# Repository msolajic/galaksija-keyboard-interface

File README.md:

# galaksija-keyboard-interface
Keyboard interface for Galaksija computer using Arduino Nano and MT8816 crosspoint switch

I will upload the code later, it is based on https://github.com/Hartland/C64-Keyboard

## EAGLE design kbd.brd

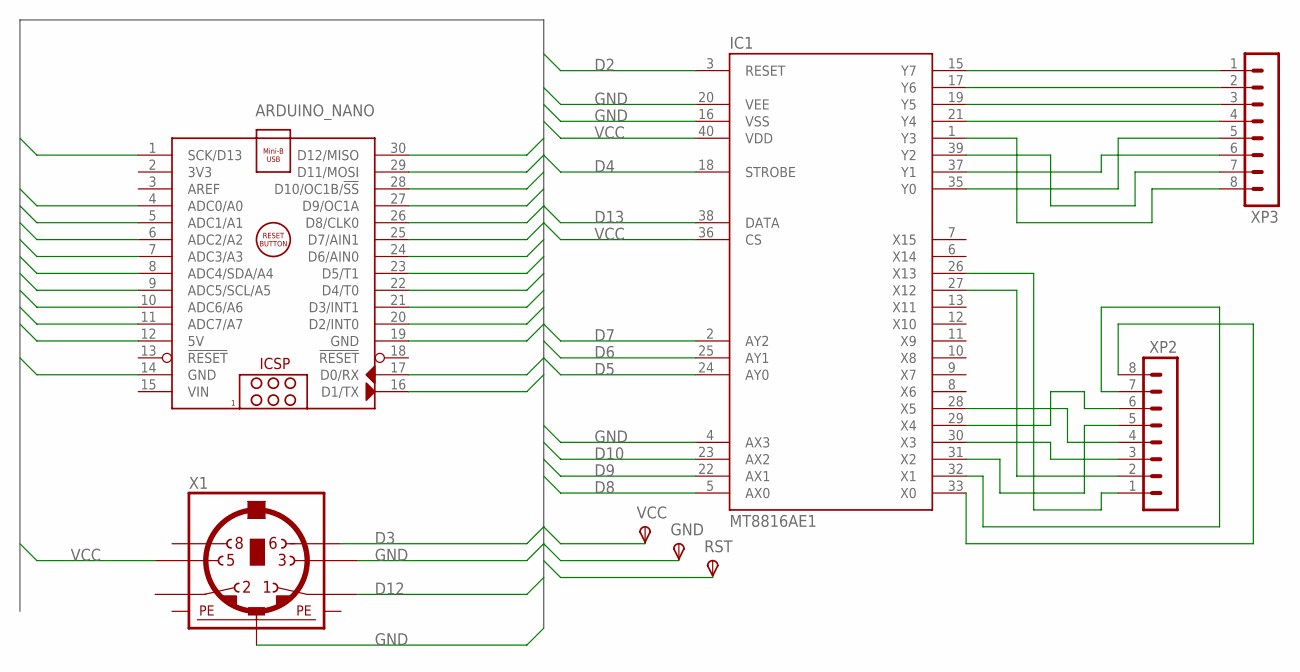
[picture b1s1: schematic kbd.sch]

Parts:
ARDUINO_NANO: ARDUINO_NANO
GND: TPSPAD1-13; P1-13
IC1: MT8816AE1; DIL40
RST: TPSPAD1-13; P1-13
VCC: TPSPAD1-13; P1-13
X1: MINI_DIN_6; M_DIN6
XP2, XP3: MA08-1

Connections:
A0: ARDUINO_NANO.4 (ADC0/A0), RST.TP
A1: ARDUINO_NANO.5 (ADC1/A1)
A2: ARDUINO_NANO.6 (ADC2/A2)
A3: ARDUINO_NANO.7 (ADC3/A3)
A4: ARDUINO_NANO.8 (ADC4/SDA/A4)
A5: ARDUINO_NANO.9 (ADC5/SCL/A5)
A6: ARDUINO_NANO.10 (ADC6/A6)
A7: ARDUINO_NANO.11 (ADC7/A7)
D0: ARDUINO_NANO.17 (D0/RX)
D1: ARDUINO_NANO.16 (D1/TX)
D2: ARDUINO_NANO.20 (D2/INT0), IC1.3 (RESET)
D3: ARDUINO_NANO.21 (D3/INT1), X1.6
D4: ARDUINO_NANO.22 (D4/T0), IC1.18 (STROBE)
D5: ARDUINO_NANO.23 (D5/T1), IC1.24 (AY0)
D6: ARDUINO_NANO.24 (D6/AIN0), IC1.25 (AY1)
D7: ARDUINO_NANO.25 (D7/AIN1), IC1.2 (AY2)
D8: ARDUINO_NANO.26 (D8/CLK0), IC1.5 (AX0)
D9: ARDUINO_NANO.27 (D9/OC1A), IC1.22 (AX1)
D10: ARDUINO_NANO.28 (D10/OC1B/!SS), IC1.23 (AX2)
D11: ARDUINO_NANO.29 (D11/MOSI)
D12: ARDUINO_NANO.30 (D12/MISO), X1.1
D13: ARDUINO_NANO.1 (SCK/D13), IC1.38 (DATA)
GND: ARDUINO_NANO.14 (GND), ARDUINO_NANO.19 (GND), GND.TP, IC1.4 (AX3), IC1.16 (VSS), IC1.20 (VEE), X1.3, X1.SH2 (PE2)
unnamed: IC1.15 (Y7), XP3.1
unnamed: IC1.17 (Y6), XP3.2
unnamed: IC1.19 (Y5), XP3.3
unnamed: IC1.21 (Y4), XP3.4
unnamed: IC1.35 (Y0), XP3.5
unnamed: IC1.37 (Y1), XP3.6
unnamed: IC1.39 (Y2), XP3.7
unnamed: IC1.1 (Y3), XP3.8
unnamed: IC1.27 (X12), XP2.2
unnamed: IC1.30 (X3), XP2.3
unnamed: IC1.28 (X5), XP2.4
unnamed: IC1.31 (X2), XP2.5
unnamed: IC1.29 (X4), XP2.6
unnamed: IC1.32 (X1), XP2.7
unnamed: IC1.33 (X0), XP2.8
unnamed: IC1.26 (X13), XP2.1
PE1: X1.SH1 (PE1)
PE3: X1.SH3 (PE3)
VCC: ARDUINO_NANO.12 (5V), IC1.36 (CS), IC1.40 (VDD), VCC.TP, X1.5
VIN: ARDUINO_NANO.15 (VIN)

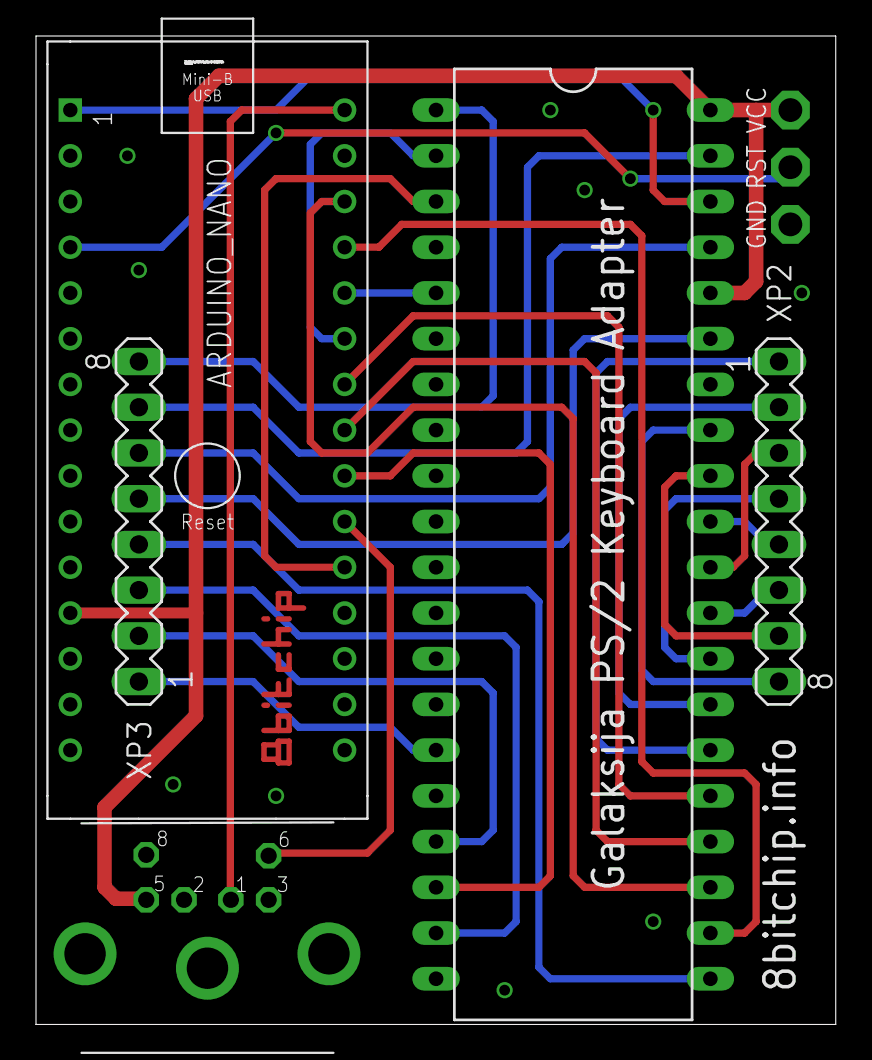
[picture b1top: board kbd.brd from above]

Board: 2 copper layers, 44.4 x 54.9 mm, 8 parts (0 on the bottom side), 30 nets.
